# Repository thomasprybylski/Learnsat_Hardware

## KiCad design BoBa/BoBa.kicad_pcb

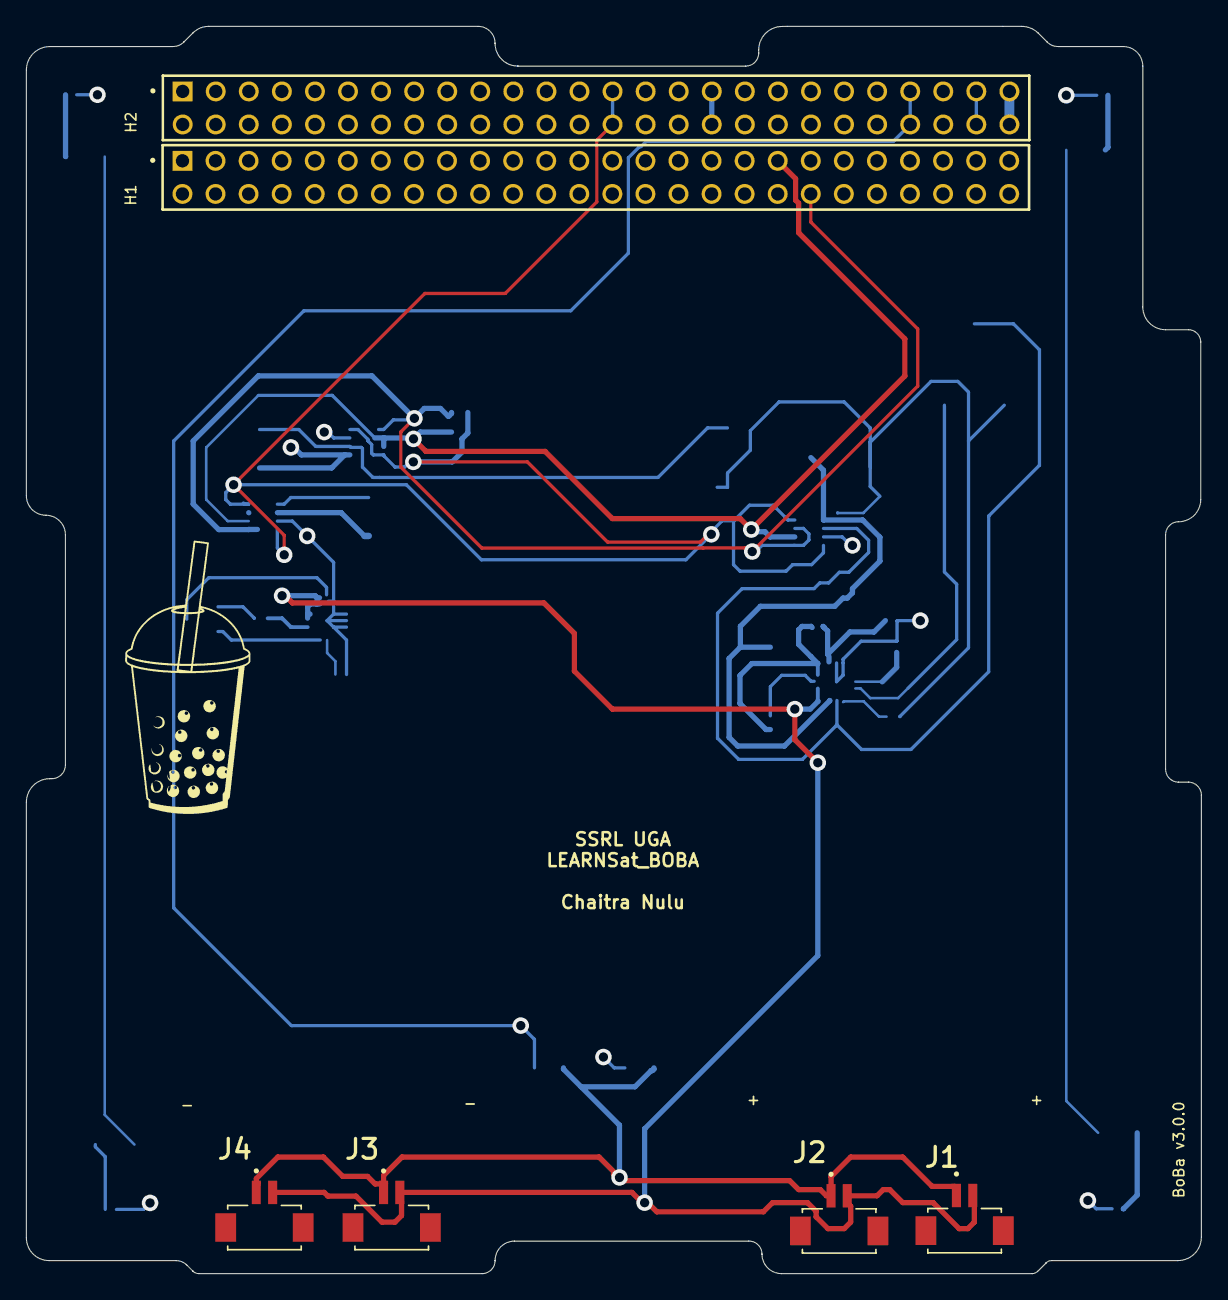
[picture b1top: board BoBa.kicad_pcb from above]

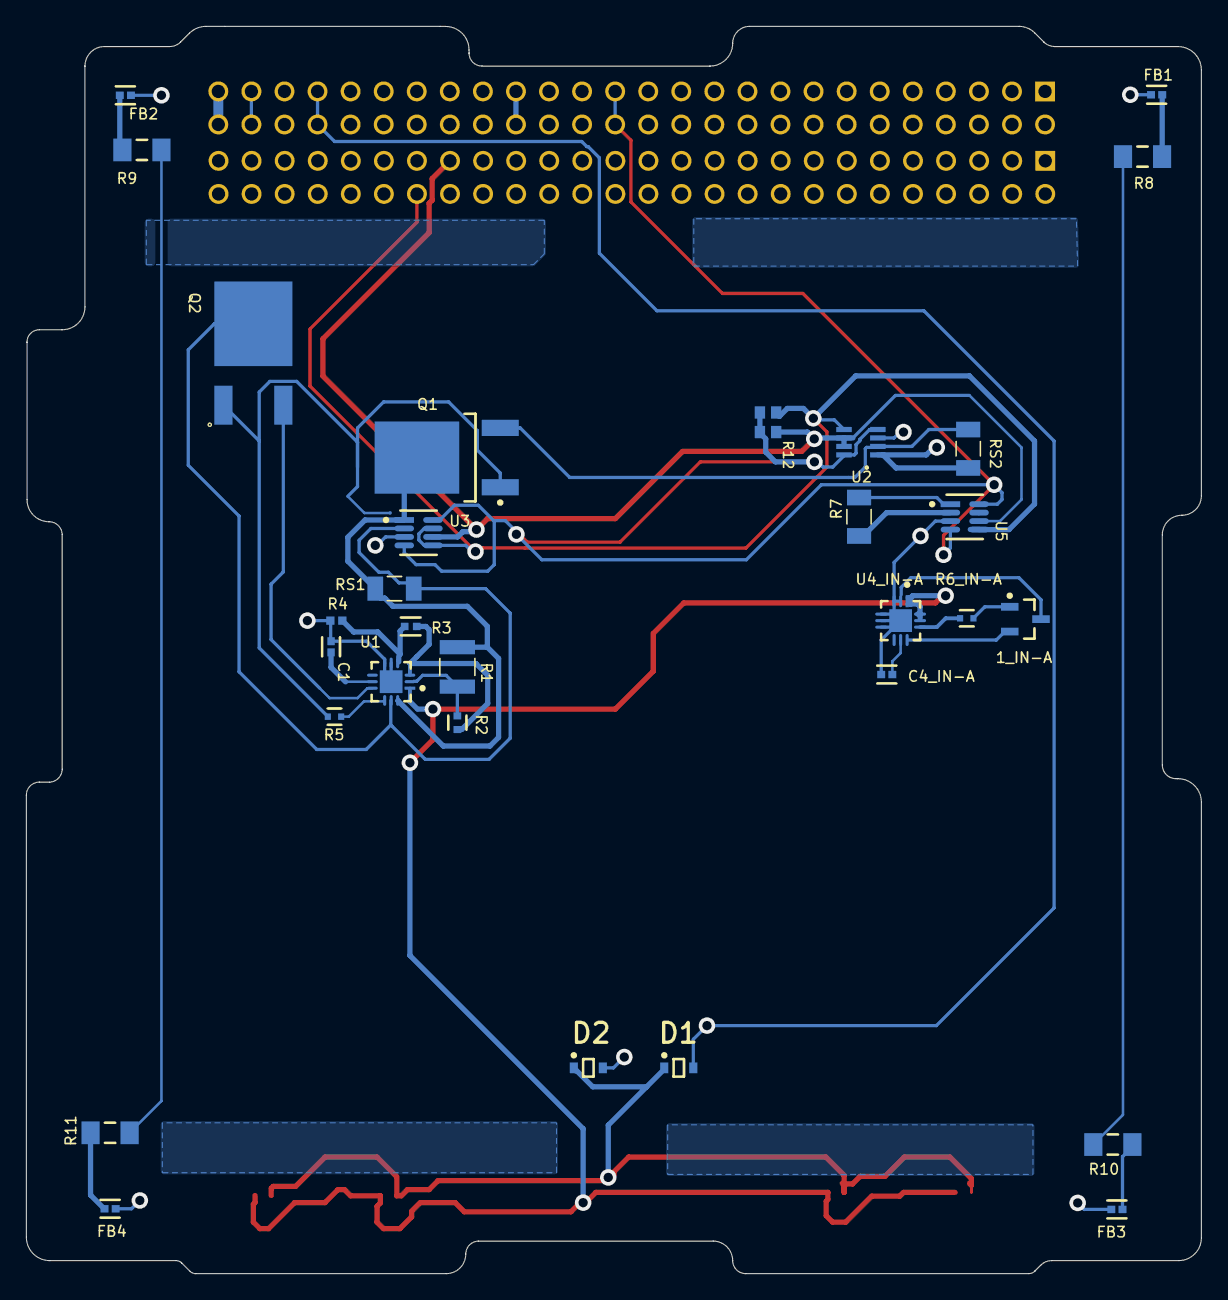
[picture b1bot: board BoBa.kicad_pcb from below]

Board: 4 copper layers, 90.3 x 95.8 mm, 37 parts (31 on the bottom side), 31 nets.

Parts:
1_IN-A: 2N7002; INF-PG-SOT23_M
  : CRCW06034K70FKTA; RESC1609X50X30NL10T20
C1, C4_IN-A: GRM155R71H472KA01D; FP-GRM155-0_05-IPC_B
D1, D2: BAT54HT1G; ONSC-SOD-323-2-477-02_V
FB1, FB2, FB3, FB4: BLM15AG102SN1D; FP-BLM15-0_05-IPC_B
H1, H2: SSQ-126-X-G-D; SAMTEC_SSQ-126-X-G-D
J1, J2, J3, J4: DF13C-2P-1.25V(21); HRS_DF13C-2P-1.25V(21)
Q1: FQD13N06LTM; FAIR-TO-252-3_V
Q2: FQD13N06LTM; TO229P991X239-3N
R1: CRCW1210900RFKTA; RESC3225X60N
R2: RG1005N-202-B-T5; FP-RG1005-MFG
R3: RG1005N-183-W-T5; FP-RG1005-IPC_B
R4: 96kOhm Resistor; CAPC1005X06N
R5, R6_IN-A: ERJ-2RKF10R0X; FP-ERJ2RK-MFG
R7: PE1206DRM470R025L1; RESC3216X89N
R8, R9, R10, R11: Resistor 1k +/-1% 1206 250 mW; RESC3116X70X50ML13T20
R12: CRCW06034K70FKTA; RESC1609X50X30NL10T20
RS1, RS2: PE1206DRM470R025L; RESC3216X89N
U1: LTC4231HUD-2#TRPBF; FP-UD-12-05-08-1855-IPC_B
U2: INA219; SOT23-8
U3, U5: INA219AIDCNR; FP-DCN0008A-IPC_B
U4_IN-A: LTC4231IUD-2#TRPBF; FP-UD-12-05-08-1855-IPC_A

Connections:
3V3_Secondary: .1, H2.27, H2.28, R12.1, U2.4, U2.8, U3.4, U3.8, U5.4, U5.8
3v3_Primary: H2.33, H2.34
Chassis GND: R8.2, R9.2, R10.2, R11.2
GND: 1_IN-A.3, C1.2, C4_IN-A.2, FB1.1, FB2.1, FB3.1, FB4.1, H2.13, H2.14, H2.29, H2.30, H2.31, H2.32, R4.2, U1.5, U1.6, U1.13, U2.3, U3.3, U4_IN-A.2, U4_IN-A.3, U4_IN-A.4, U4_IN-A.5, U4_IN-A.6, U4_IN-A.13, U5.3
G_IN-G: 1_IN-A.1, R6_IN-A.1
I2C Clock: .2, H1.40, U2.5, U3.5, U3.7, U5.5, U5.7
I2C Data: H1.37, R12.2, U2.6, U2.7, U3.6, U5.6
INHIBIT: J1.2, J2.2, J3.2, J4.2, U1.1, U4_IN-A.1, U4_IN-A.11, U4_IN-A.12
NetC1_1: C1.1, U1.8
NetC4_IN-G_1: C4_IN-A.1, U4_IN-A.8
NetD1_1: D1.1, D2.1, J1.1, J2.1, J3.1, J4.1
NetFB1_2: FB1.2, R8.1
NetFB2_2: FB2.2, R9.1
NetFB3_2: FB3.2, R10.1
NetFB4_2: FB4.2, R11.1
NetQ1_4: Q1.4, R1.2, RS1.1, U1.12, U3.1
NetQ2_1: Q1.1, Q2.1, R5.1
NetQ2_3: Q2.3, U1.9
NetQ2_4: Q2.4, RS1.2, U1.11, U3.2
NetR1_1: R1.1, R2.1, U1.2
NetR2_2: R2.2, R3.1, U1.3
NetR3_2: R3.2, R4.1, U1.4
NetR5_2: R5.2, U1.10
NetR6_IN-G_2: R6_IN-A.2, U4_IN-A.10
NetR7_1: R7.1, U5.2
NetR7_2: R7.2, U5.1
Pack+_Neg: H2.51, H2.52
Pack+_Pos: D2.2, RS2.1, U2.1
Pack-_Neg: 1_IN-A.2, Q1.3, RS2.2, U2.2, U4_IN-A.9
VBatt: H2.49, H2.50
Vmppt: D1.2, H2.45, H2.46

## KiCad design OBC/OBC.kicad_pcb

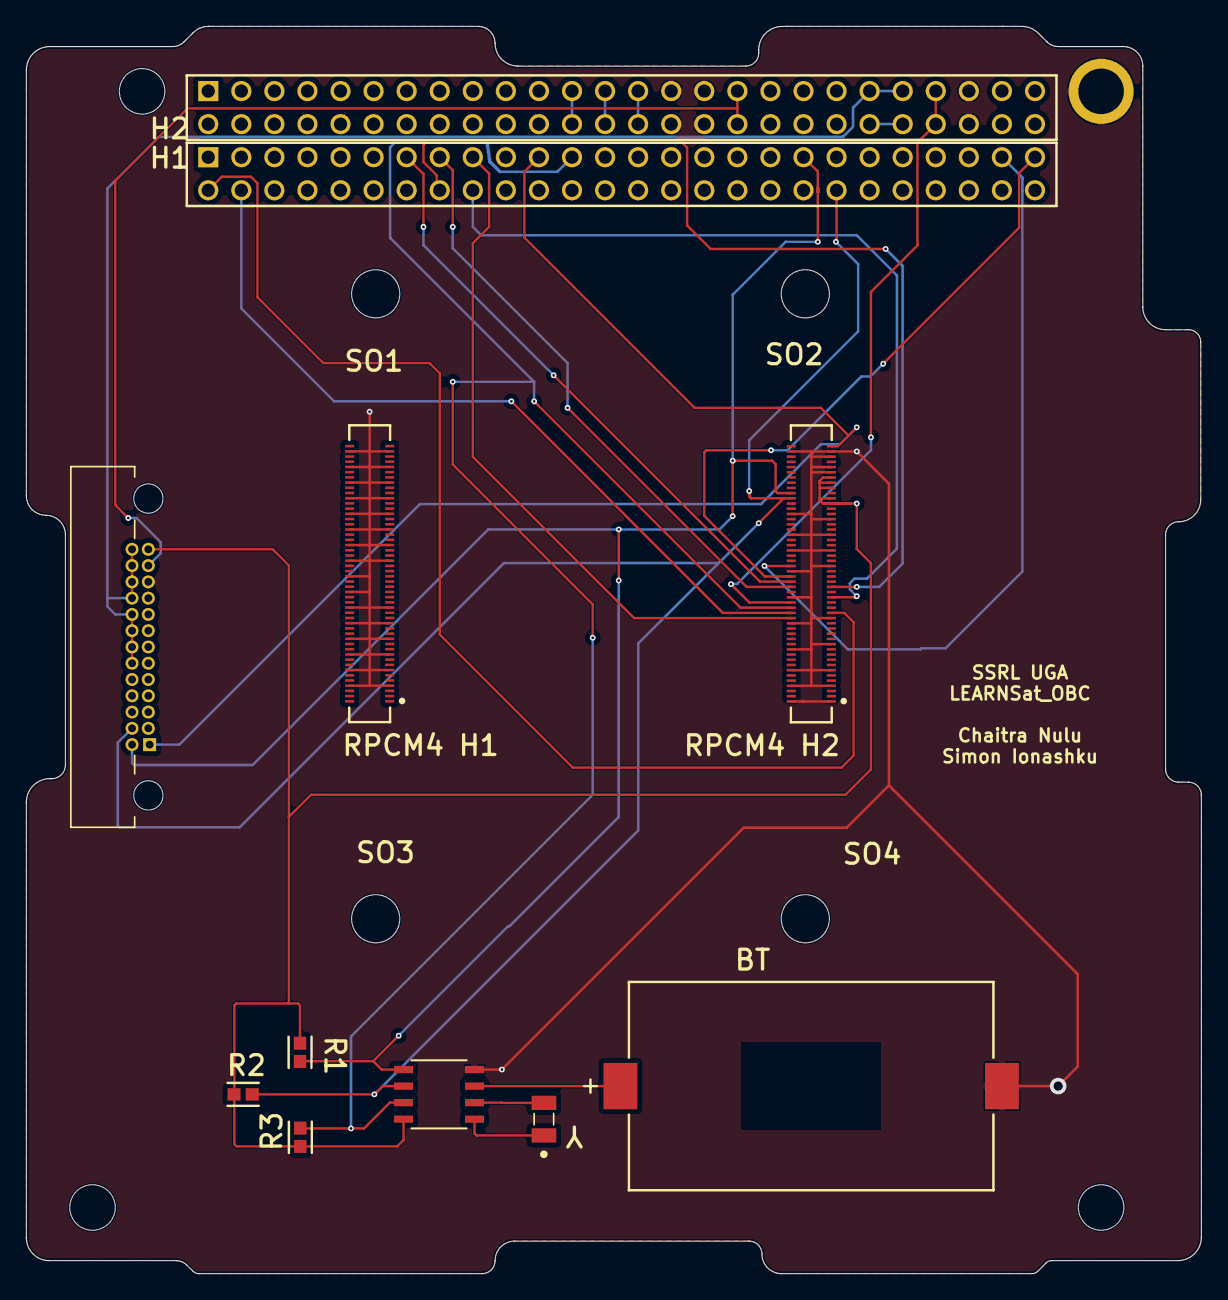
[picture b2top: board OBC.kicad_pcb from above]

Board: 4 copper layers, 90.3 x 95.8 mm, 9 parts (0 on the bottom side), 21 nets.

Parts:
BT: BA2032SM; MPD-BA2032SM_V
H1, H2: SSQ-126-22-G-D; SMTC-SSQ-126-22-X-D
R1, R2, R3: Comment; FP-RMCF0603-IPC_B
RPCM4 H1, RPCM4 H2: Comment; FP-DF40HC_3_0_-100DS-0_4V-MFG
Y: ECS-.327-12.5-34RR-TR; XTAL_ECS-.327-12.5-34RR-TR

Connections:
3V3_Primary: H2.33, H2.34
3V3_Secondary: H2.27, H2.28
5V_Primary: H2.23, H2.24, R1.1, R2.1, R3.1, RPCM4 H2.77, RPCM4 H2.79, RPCM4 H2.83, RPCM4 H2.85, RPCM4 H2.87
5V_Secondary: H2.25, H2.26
GND: BT.2, H2.29, H2.30, H2.31, H2.32, H2.47, H2.48, RPCM4 H1.7, RPCM4 H1.8, RPCM4 H1.13, RPCM4 H1.14, RPCM4 H1.19, RPCM4 H1.20, RPCM4 H1.25, RPCM4 H1.26, RPCM4 H1.31, RPCM4 H1.32, RPCM4 H1.37, RPCM4 H1.38, RPCM4 H1.44, RPCM4 H1.50, RPCM4 H1.55, RPCM4 H1.56, RPCM4 H1.61, RPCM4 H1.62, RPCM4 H1.67, RPCM4 H1.68, RPCM4 H1.73, RPCM4 H1.74, RPCM4 H1.79, RPCM4 H1.80, RPCM4 H1.85, RPCM4 H1.86, RPCM4 H1.91, RPCM4 H1.92, RPCM4 H1.97, RPCM4 H1.98, RPCM4 H2.1, RPCM4 H2.2, RPCM4 H2.7, RPCM4 H2.8, RPCM4 H2.13, RPCM4 H2.14, RPCM4 H2.22, RPCM4 H2.23, RPCM4 H2.32, RPCM4 H2.33, RPCM4 H2.42, RPCM4 H2.52, RPCM4 H2.53, RPCM4 H2.59, RPCM4 H2.60, RPCM4 H2.65, RPCM4 H2.66, RPCM4 H2.71, RPCM4 H2.74, RPCM4 H2.89, RPCM4 H2.91, RPCM4 H2.95, RPCM4 H2.97, RPCM4 H2.98
GPIO 4: H1.49, RPCM4 H2.54
GPIO 5: H1.17, RPCM4 H2.34
GPIO 17: H1.51, RPCM4 H2.50
GPIO 22: H1.15, RPCM4 H2.46
GPIO 24: H1.16, RPCM4 H2.45
GPIO 25: H1.18, RPCM4 H2.41
GPIO 27: H1.13, RPCM4 H2.48
OBC_HB: H1.23, R3.2, RPCM4 H2.38
OBC_RST: H1.21, RPCM4 H2.99
SCL: H1.40, R2.2, RPCM4 H2.80
SDA: H1.37, R1.2, RPCM4 H2.82
UART_RX: H1.4, RPCM4 H2.36
UART_TX: H1.2, RPCM4 H2.35
VBATT_Primary: H2.41, H2.43
VBATT_Secondary: H2.42, H2.44
Vmppt: H2.45, H2.46, RPCM4 H2.40

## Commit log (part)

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2025-10-15 Managed project "LEARNSAT_POBOY_3.2.0" created from AD
2025-10-15 Created new Project with all the files
2025-10-16 Created new Project with all the files (auto)
2026-02-09 LearnSat OBC Folder
2026-02-09 LearnSat OBC Initial Commit
2026-02-09 LearnSat OBC Organized Folder
2026-03-25 Create LEARNSAT_PoBoI
2026-04-04 Changed diode D?1 to D23 as a git test
2026-04-04 Small global net changes
2026-04-04 Replaced local nets with global and left local nets intact
2026-04-06 minor net changes
2026-04-07 MEMESAT_PoBoI
2026-04-10 Added footprints to schematic
2026-04-11 Add .history to gitignore
2026-04-11 Added footprints
2026-04-11 Revert "Added footprints"
    This reverts commit 60874dc990646fe1cd7d1fb5545adb6bd8132b81.
2026-04-17 minor naming changes
2026-04-17 retried naming changes
2026-04-17 Add gitignore
2026-04-17 removed solar telemetry
2026-04-17 updated pcb from schematic
2026-04-19 moved files to right location
2026-04-19 routed 12VPrimary
2026-04-20 routed 12V Boost
2026-04-20 Edited 12V Rail schematics
2026-04-20 routed primary rails
2026-04-20 DRC Folder
2026-04-20 brought back 12V_Boost
2026-04-20 routed VBATTPrimary
2026-04-20 remove stray boost converter file
